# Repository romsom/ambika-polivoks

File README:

Polivoks voicecard for the Mutable Instruments Ambika synthesizer.

Based on work by Olivier Gillet - http://www.mutable-instruments.net/.

Developed by Krzysztof Iwanowski.

The firmware is released under a GPL3.0 license.

The PCB layouts and schematics are released under a Creative Commons cc-by-sa 3.0 license.

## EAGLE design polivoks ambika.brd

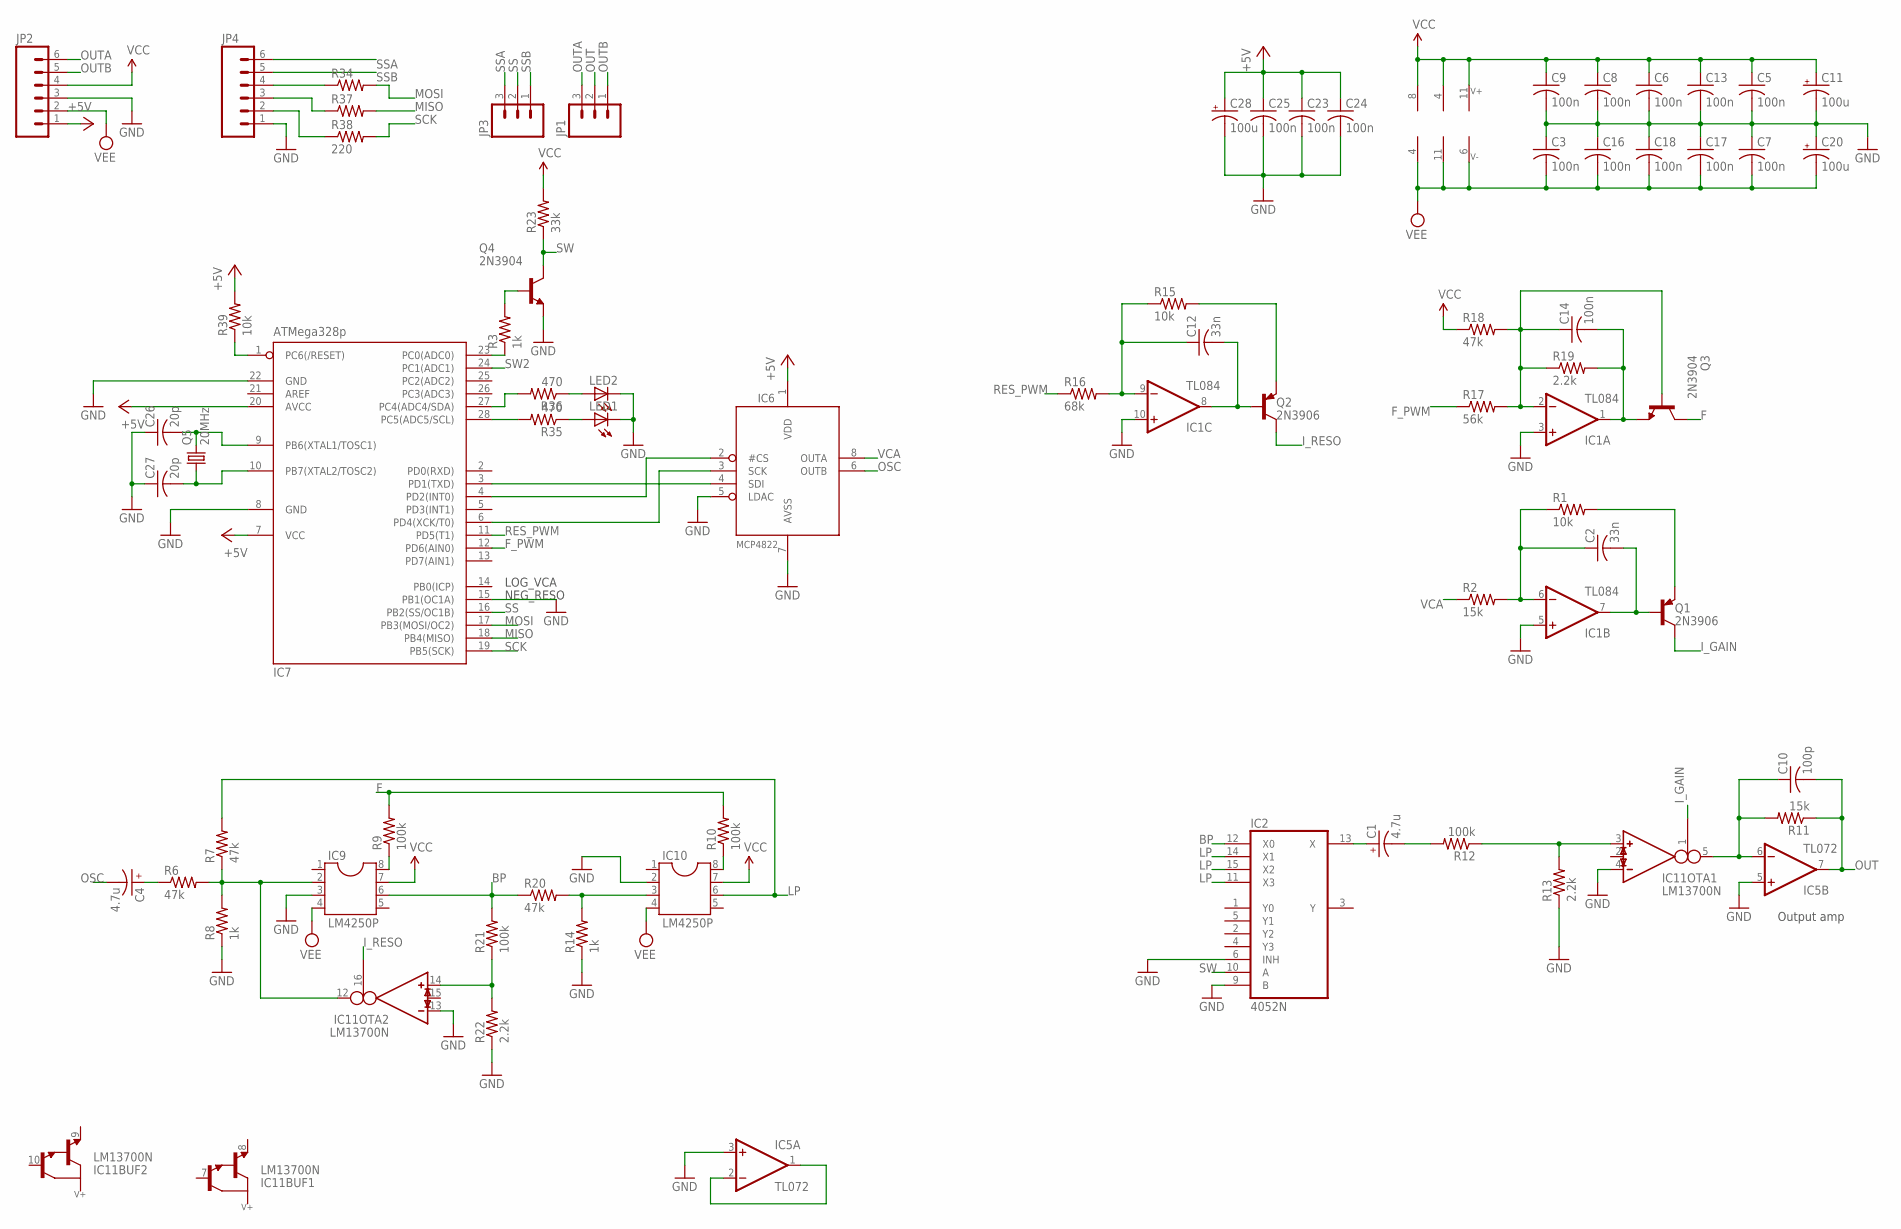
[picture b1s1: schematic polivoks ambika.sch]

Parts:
C1, C4: 4.7u; E11-6.3
C2, C12: 33n; C050-025X075
C3, C5, C6, C7, C8, C9, C13, C14, C16, C17, C18, C23, C24, C25: 100n; C025-025X050
C10: 100p; C025-025X050
C11, C20, C28: 100u; E2,5-6
C26, C27: 20p; C025-024X044
IC1: TL084; DIL14
IC2: 4052N; DIL16
IC5: TL072; DIL08
IC6: MCP4822; DIL08
IC7: ATMega328p; DIL28-3
IC9, IC10: LM4250P; DIL08
IC11: LM13700N; DIL16
JP1, JP3: M03PTH; 1X03
JP2, JP4: M06SIP; 1X06
LED1, LED2: LED3MM
Q1, Q2: 2N3906; TO92-
Q3, Q4: 2N3904; TO92
Q5: 20MHz; HC49U-V
R1, R15, R39: 10k; 0204/7
R2, R11: 15k; 0204/7
R3, R8, R14: 1k; 0204/7
R6, R7, R18, R20: 47k; 0204/7
R9, R10, R12, R21: 100k; 0204/7
R13, R19, R22: 2.2k; 0204/7
R16: 68k; 0204/7
R17: 56k; 0204/7
R23: 33k; 0204/7
R34, R37, R38: 220; 0204/7
R35, R36: 470; 0204/7

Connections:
+5V: C23.1, C24.1, C25.1, C28.+, IC6.1 (VDD), IC7.7 (VCC), IC7.20 (AVCC), JP2.1, R39.2
BP: IC2.12 (X0), IC9.6, R20.1, R21.2
F: Q3.1 (C), R9.2, R10.2
F_PWM: IC7.12 (PD6(AIN0)), R17.1
GND: C3.1, C5.2, C6.2, C7.1, C8.2, C9.2, C11.-, C13.2, C16.1, C17.1, C18.1, C20.+, C23.2, C24.2, C25.2, C26.1, C27.1, C28.-, IC1.3 (+IN), IC1.5 (+IN), IC1.10 (+IN), IC2.6 (INH), IC2.8 (GND), IC2.9 (B), IC5.3 (+IN), IC5.5 (+IN), IC6.5 (LDAC), IC6.7 (AVSS), IC7.8 (GND), IC7.15 (PB1(OC1A)), IC7.22 (GND), IC9.3, IC10.2, IC11.4 (IN_N), IC11.13 (IN_N), JP2.3, JP4.1, LED1.K (C), LED2.K (C), Q4.3 (E), R8.1, R13.1, R14.1, R22.1
I_GAIN: IC11.1 (I_BIAS), Q1.1 (C)
I_RESO: IC11.16 (I_BIAS), Q2.1 (C)
LP: IC2.11 (X3), IC2.14 (X1), IC2.15 (X2), IC10.6, R7.2
MISO: IC7.18 (PB4(MISO)), R37.2
MOSI: IC7.17 (PB3(MOSI/OC2)), R34.2
unnamed: IC9.2, IC11.12 (OUT), R6.2, R7.1, R8.2
unnamed: C14.2, IC1.1 (OUT), Q3.3 (E), R19.2
unnamed: IC6.4 (SDI), IC7.3 (PD1(TXD))
unnamed: C4.+ (1), R6.1
unnamed: C1.+ (1), IC2.13 (X)
unnamed: IC10.3, R14.2, R20.2
unnamed: LED1.A, R35.1
unnamed: JP4.2, R38.1
unnamed: IC9.8, R9.1
unnamed: LED2.A, R36.1
unnamed: IC7.27 (PC4(ADC4/SDA)), R36.2
unnamed: C1.- (2), R12.2
unnamed: JP4.3, R37.1
unnamed: IC7.1 (PC6(/RESET)), R39.1
unnamed: IC6.3 (SCK), IC7.6 (PD4(XCK/T0))
unnamed: IC6.2 (#CS), IC7.4 (PD2(INT0))
unnamed: IC10.8, R10.1
unnamed: JP4.4, R34.1
unnamed: IC11.14 (IN_P), R21.1, R22.2
unnamed: IC7.28 (PC5(ADC5/SCL)), R35.2
unnamed: Q4.2 (B), R3.2
unnamed: IC5.1 (OUT), IC5.2 (-IN)
unnamed: IC7.23 (PC0(ADC0)), R3.1
unnamed: C12.2, IC1.8 (OUT), Q2.2 (B)
unnamed: C2.2, IC1.7 (OUT), Q1.2 (B)
unnamed: IC11.3 (IN_P), R12.1, R13.2
unnamed: C14.1, IC1.2 (-IN), Q3.2 (B), R17.2, R18.2, R19.1
unnamed: C2.1, IC1.6 (-IN), R1.1, R2.2
unnamed: C12.1, IC1.9 (-IN), R15.1, R16.2
unnamed: Q2.3 (E), R15.2
unnamed: Q1.3 (E), R1.2
unnamed: C10.1, IC5.6 (-IN), IC11.5 (OUT), R11.2
unnamed: C27.2, IC7.10 (PB7(XTAL2/TOSC2)), Q5.1
unnamed: C26.2, IC7.9 (PB6(XTAL1/TOSC1)), Q5.2
OSC: C4.- (2), IC6.6 (OUTB)
OUT: C10.2, IC5.7 (OUT), JP1.2, R11.1
OUTA: JP1.3, JP2.6
OUTB: JP1.1, JP2.5
RES_PWM: IC7.11 (PD5(T1)), R16.1
SCK: IC7.19 (PB5(SCK)), R38.2
SS: IC7.16 (PB2(SS/OC1B)), JP3.2
SSA: JP3.3, JP4.6
SSB: JP3.1, JP4.5
SW: IC2.10 (A), Q4.1 (C), R23.1
SW2: IC7.24 (PC1(ADC1))
VCA: IC6.8 (OUTA), R2.1
VCC: C5.1, C6.1, C8.1, C9.1, C11.+, C13.1, IC1.4 (V+), IC2.16 (VCC), IC5.8 (V+), IC9.7, IC10.7, IC11.11 (V+), JP2.4, R18.1, R23.2
VEE: C3.2, C7.2, C16.2, C17.2, C18.2, C20.-, IC1.11 (V-), IC2.7 (VEE), IC5.4 (V-), IC9.4, IC10.4, IC11.6 (V-), JP2.2

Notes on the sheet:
LOG_VCA
NEG_RESO
Output amp

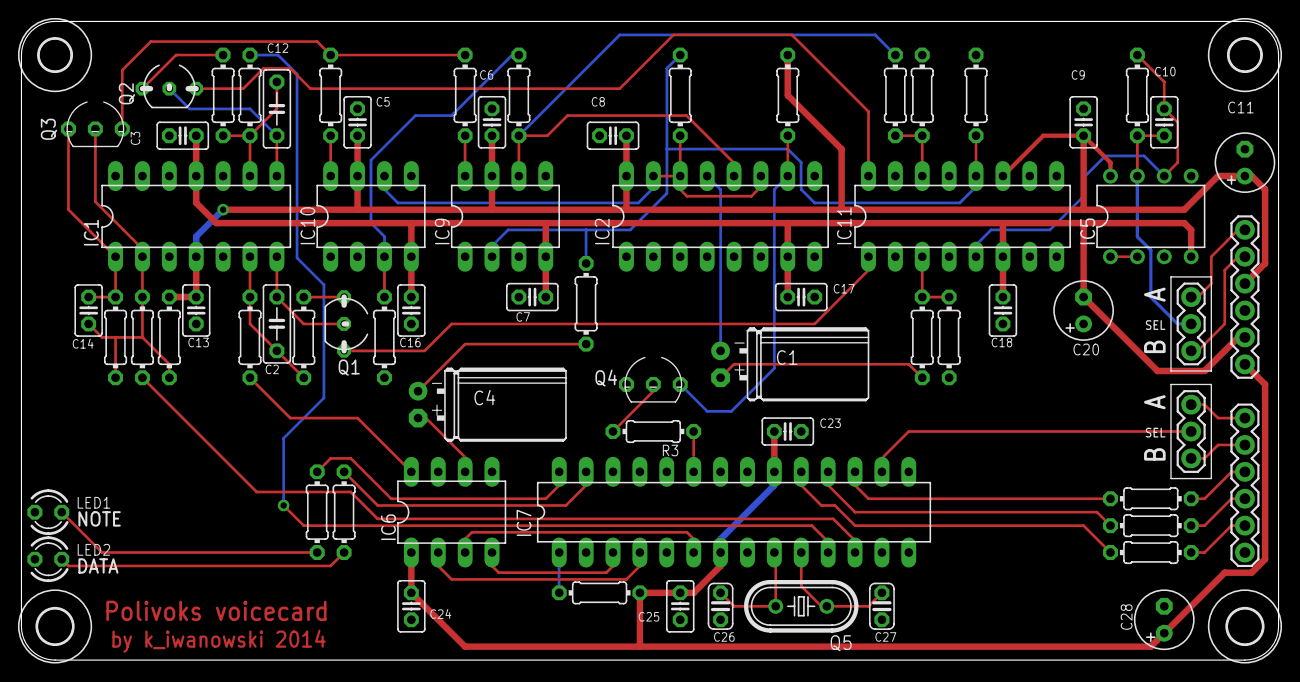
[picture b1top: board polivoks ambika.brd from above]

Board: 2 copper layers, 118.7 x 60.3 mm, 74 parts (0 on the bottom side), 57 nets.

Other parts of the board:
U$1, U$2: 3,0
U$4, U$5: 3,3

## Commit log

2014-12-29 first
2015-03-17 Added the firmware
2015-04-06 deleted a few unnecessary files
2015-07-20 Added a resistor to limit the current on BP mode
2020-04-13 committing local changes from imported zip, retaining UNIX line breaks in source files
